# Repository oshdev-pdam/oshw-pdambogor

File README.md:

# oshw-pdambogor

Repositori rintisan untuk OSH Development sensor tekanan air untuk PDAM Kota Bogor

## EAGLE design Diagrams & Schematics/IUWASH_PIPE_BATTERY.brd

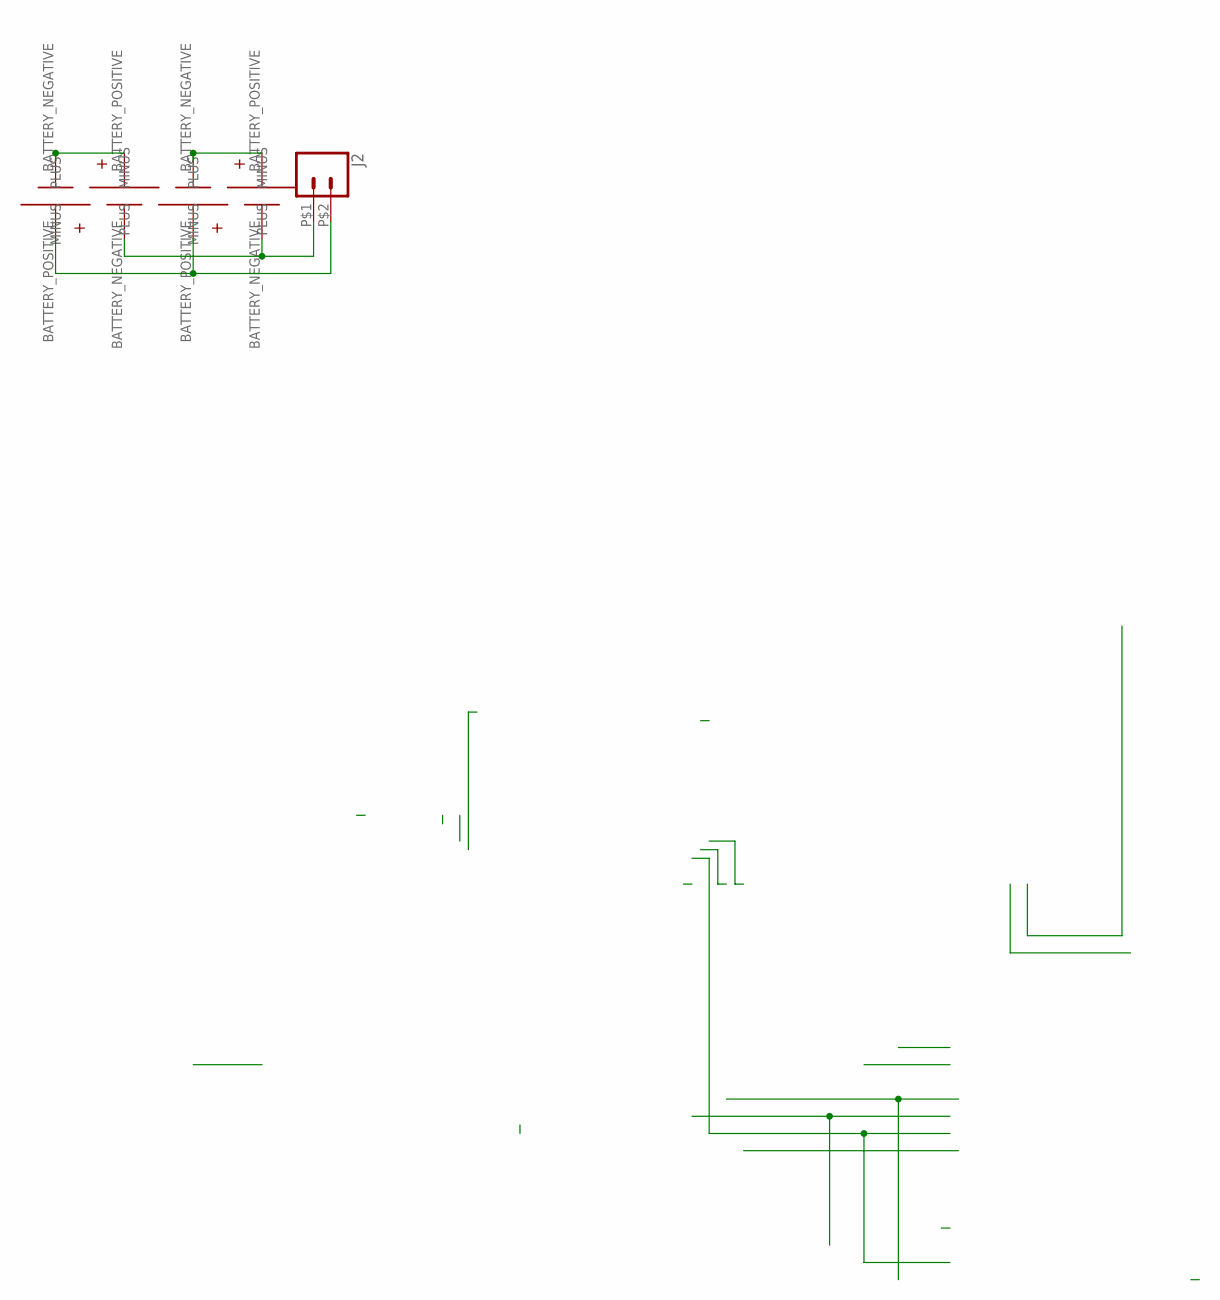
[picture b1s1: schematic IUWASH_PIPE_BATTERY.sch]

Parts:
J2: CONN_02PTH2; 1X02_BIG
U$4, U$5, U$6, U$7: SMT18650; 18650SMT

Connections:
unnamed: J2.P$1 (1), U$5.BATTERY_NEGATIVE (MINUS), U$7.BATTERY_NEGATIVE (MINUS)
unnamed: J2.P$2 (2), U$4.BATTERY_POSITIVE (PLUS), U$6.BATTERY_POSITIVE (PLUS)
unnamed: U$4.BATTERY_NEGATIVE (MINUS), U$5.BATTERY_POSITIVE (PLUS)
unnamed: U$6.BATTERY_NEGATIVE (MINUS), U$7.BATTERY_POSITIVE (PLUS)

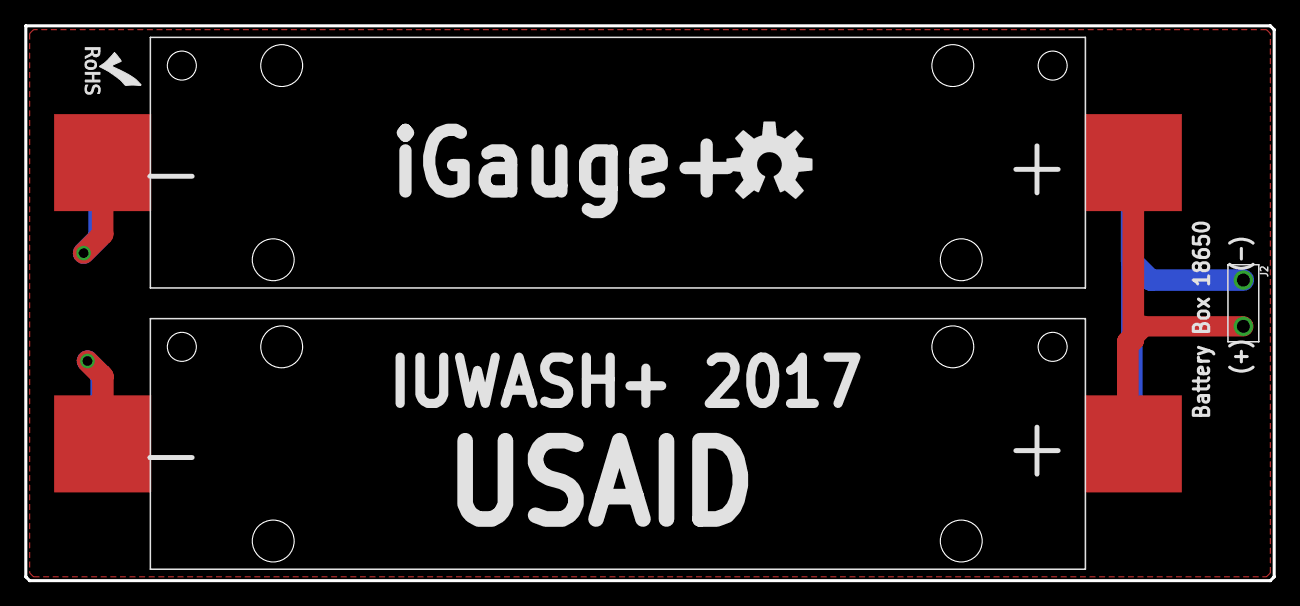
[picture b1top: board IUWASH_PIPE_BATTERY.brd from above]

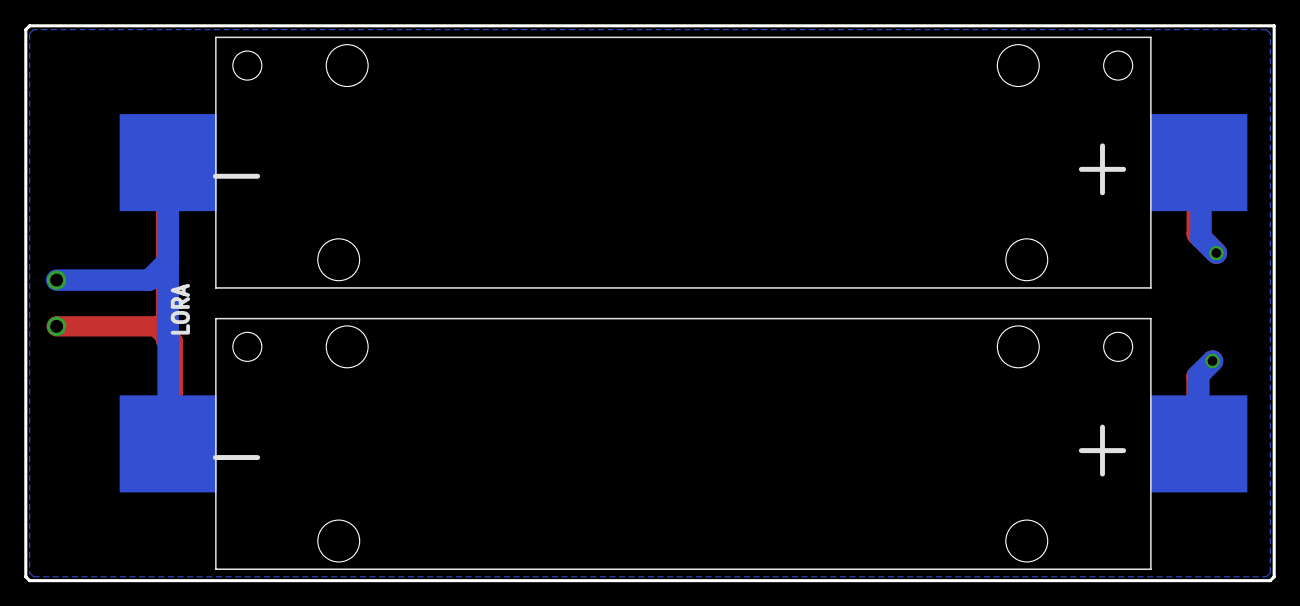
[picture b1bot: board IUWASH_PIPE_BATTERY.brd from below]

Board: 2 copper layers, 102.9 x 45.7 mm, 7 parts (2 on the bottom side), 4 nets.

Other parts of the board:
U$1: OSHW-LOGO-L
U$12: ROHS_LOGO_0.18_IN

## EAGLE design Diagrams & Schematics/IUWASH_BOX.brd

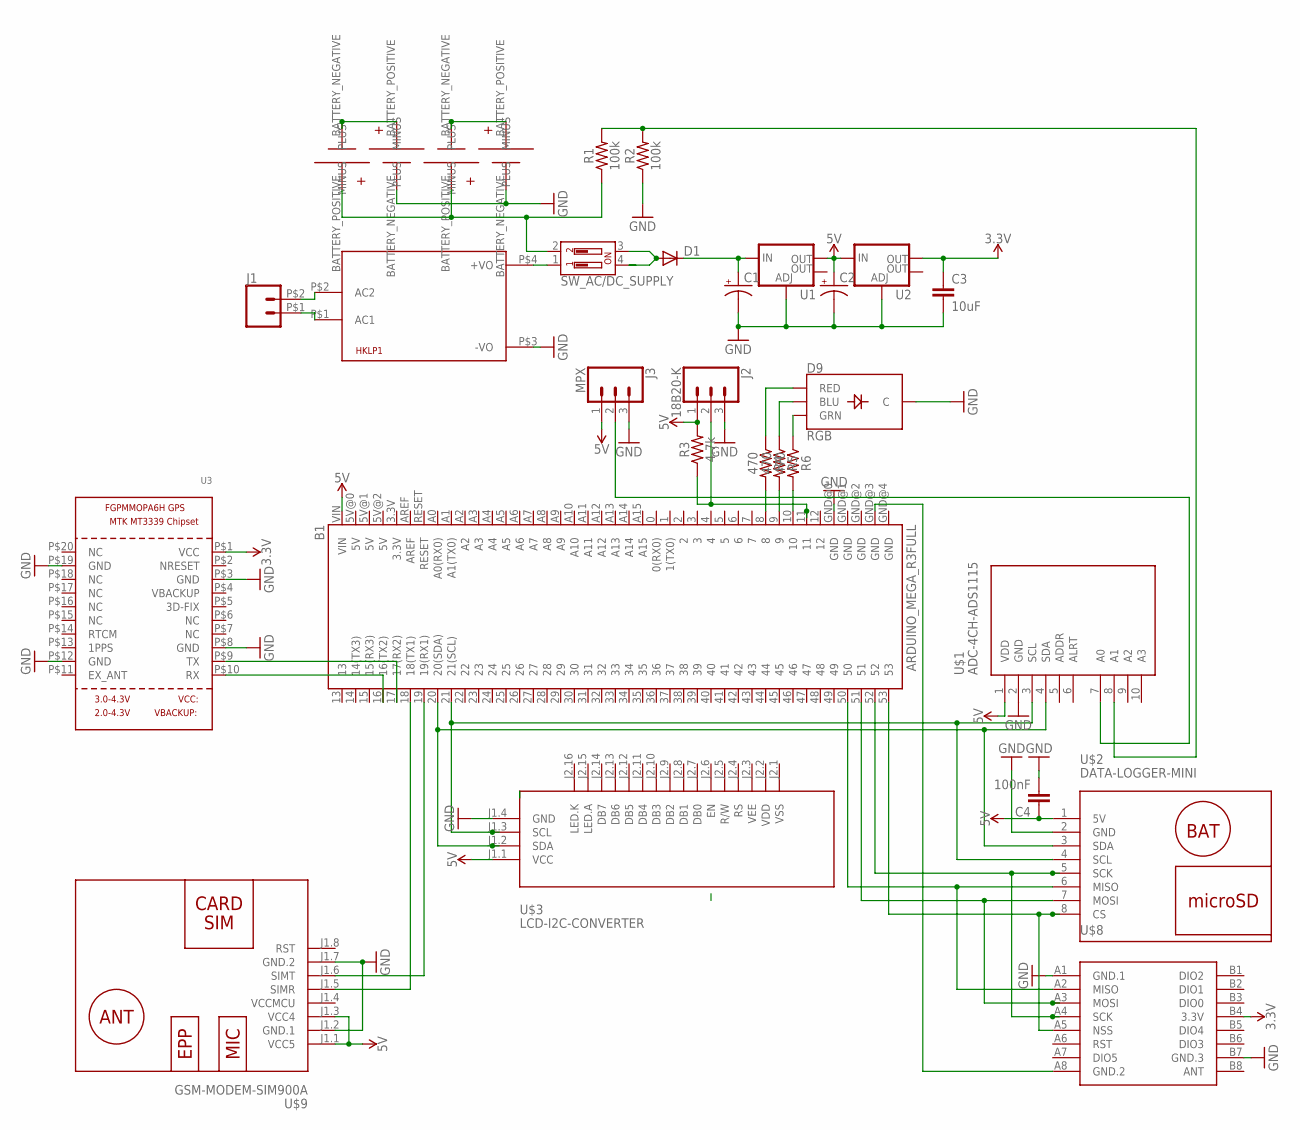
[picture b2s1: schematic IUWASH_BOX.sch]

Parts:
B1: ARDUINO_MEGA_R3FULL; ARDUINO_MEGA
C1, C2: CPOL-USE; PANASONIC_E
C3: 10uF; 0603
C4: 100nF; 0603
D1: DIODE-SOD106-W; SOD106-W
D9: RGB; LED-RGB-THRU
HKLP1: HKLPM01
J1: CONN_02PTH2; 1X02_BIG
J2: 18B20-K; SCREWTERMINAL-3.5MM-3
J3: MPX; SCREWTERMINAL-3.5MM-3
R1, R2: 100k; 0603
R3: 4.7k; 0603
R4, R5, R6: 470; 0603
SW_AC/DC_SUPPLY: DIP-02-PTH-100MIL; DIPSWITCH-02-209-2LPST
U1, U2: V_REG_LM1117SOT223; SOT223
U3: GPS_FGPMMOPA6H; FGPMMOPA6H
U$1: ADC-4CH-ADS1115
U$2: DATA-LOGGER-MINI
U$3: LCD-I2C-CONVERTER
U$4, U$5, U$6, U$7: SMT18650; 18650SMT
U$8: WIRELESS-LORA-RFM95W#SMD
U$9: GSM-MODEM-SIM900A

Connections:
3.3V: C3.1, U2.2 (OUT), U3.P$1 (VCC), U$8.B4 (3.3V)
5V: B1.VIN, C2.+, C4.1, J2.1, J3.1, R3.2, U1.2 (OUT), U2.3 (IN), U$1.1 (VDD), U$2.1 (5V), U$3.J1.1 (VCC), U$9.J1.1 (VCC5), U$9.J1.3 (VCC4)
GND: C4.2, HKLP1.P$3 (-VO), J3.3, R2.1, U3.P$3 (GND), U3.P$8 (GND), U3.P$12 (GND), U3.P$19 (GND), U$2.2 (GND), U$3.J1.4 (GND), U$5.BATTERY_NEGATIVE (MINUS), U$7.BATTERY_NEGATIVE (MINUS), U$8.A1 (GND.1), U$8.B7 (GND.3), U$9.J1.2 (GND.1), U$9.J1.7 (GND.2)
unnamed: C1.+, D1.C, U1.3 (IN)
unnamed: B1.50, U$2.6 (MISO), U$8.A2 (MISO)
unnamed: D1.A, SW_AC/DC_SUPPLY.3, SW_AC/DC_SUPPLY.4
unnamed: HKLP1.P$4 (+VO), SW_AC/DC_SUPPLY.1
unnamed: HKLP1.P$1 (AC1), J1.P$1 (1)
unnamed: HKLP1.P$2 (AC2), J1.P$2 (2)
unnamed: D9.3 (GRN), R6.1
unnamed: J3.2, U$1.7 (A0)
unnamed: R1.1, SW_AC/DC_SUPPLY.2, U$4.BATTERY_POSITIVE (PLUS), U$6.BATTERY_POSITIVE (PLUS)
unnamed: U$4.BATTERY_NEGATIVE (MINUS), U$5.BATTERY_POSITIVE (PLUS)
unnamed: U$6.BATTERY_NEGATIVE (MINUS), U$7.BATTERY_POSITIVE (PLUS)
unnamed: R1.2, R2.2, U$1.8 (A1)
unnamed: B1.17 (17(RX2)), U3.P$9 (TX)
unnamed: B1.52, U$2.5 (SCK), U$8.A4 (SCK)
unnamed: B1.51, U$2.7 (MOSI), U$8.A3 (MOSI)
unnamed: B1.16 (16(TX2)), U3.P$10 (RX)
unnamed: B1.GND@3 (GND), U$8.A8 (GND.2)
unnamed: B1.19 (19(RX1)), U$9.J1.6 (SIMT)
unnamed: B1.20 (20(SDA)), U$1.4 (SDA), U$2.3 (SDA), U$3.J1.2 (SDA)
unnamed: B1.21 (21(SCL)), U$1.3 (SCL), U$2.4 (SCL), U$3.J1.3 (SCL)
unnamed: B1.53, U$2.8 (CS), U$8.A5 (NSS)
unnamed: B1.18 (18(TX1)), U$9.J1.5 (SIMR)
unnamed: B1.8, R4.2
unnamed: B1.11, J2.2, R3.1
unnamed: B1.9, R5.2
unnamed: D9.4 (BLU), R5.1
unnamed: D9.1 (RED), R4.1
unnamed: B1.10, R6.2
unnamed: B1.GND@0 (GND), C1.-, C2.-, C3.2, D9.2 (C), J2.3, U1.1 (ADJ), U2.1 (ADJ), U$1.2 (GND)
VCCMCU: U$9.J1.4 (VCCMCU)

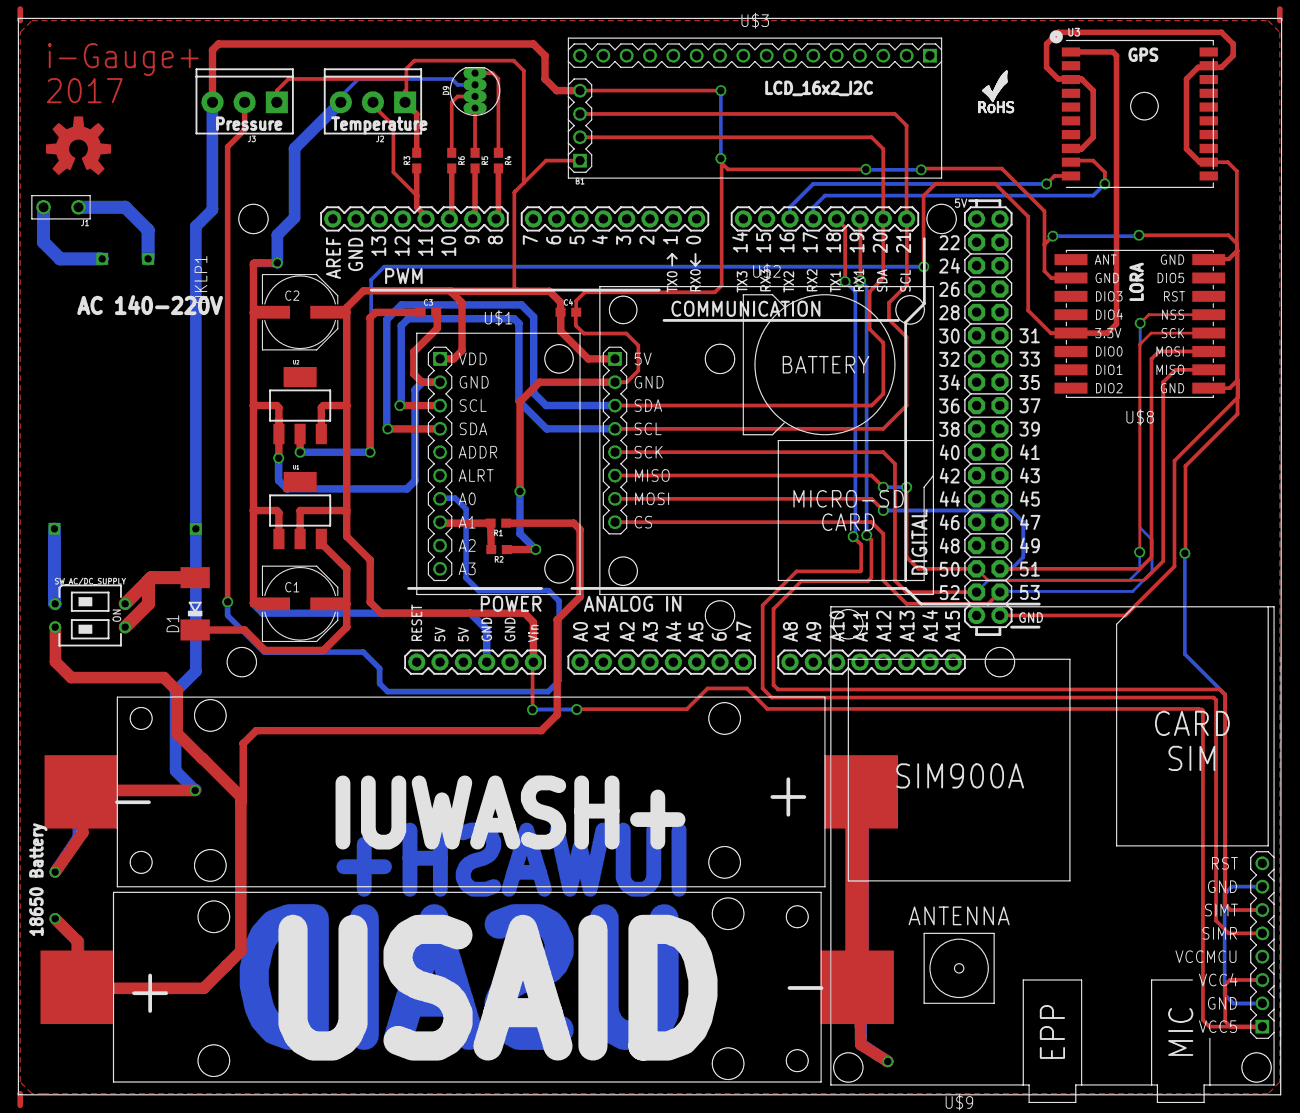
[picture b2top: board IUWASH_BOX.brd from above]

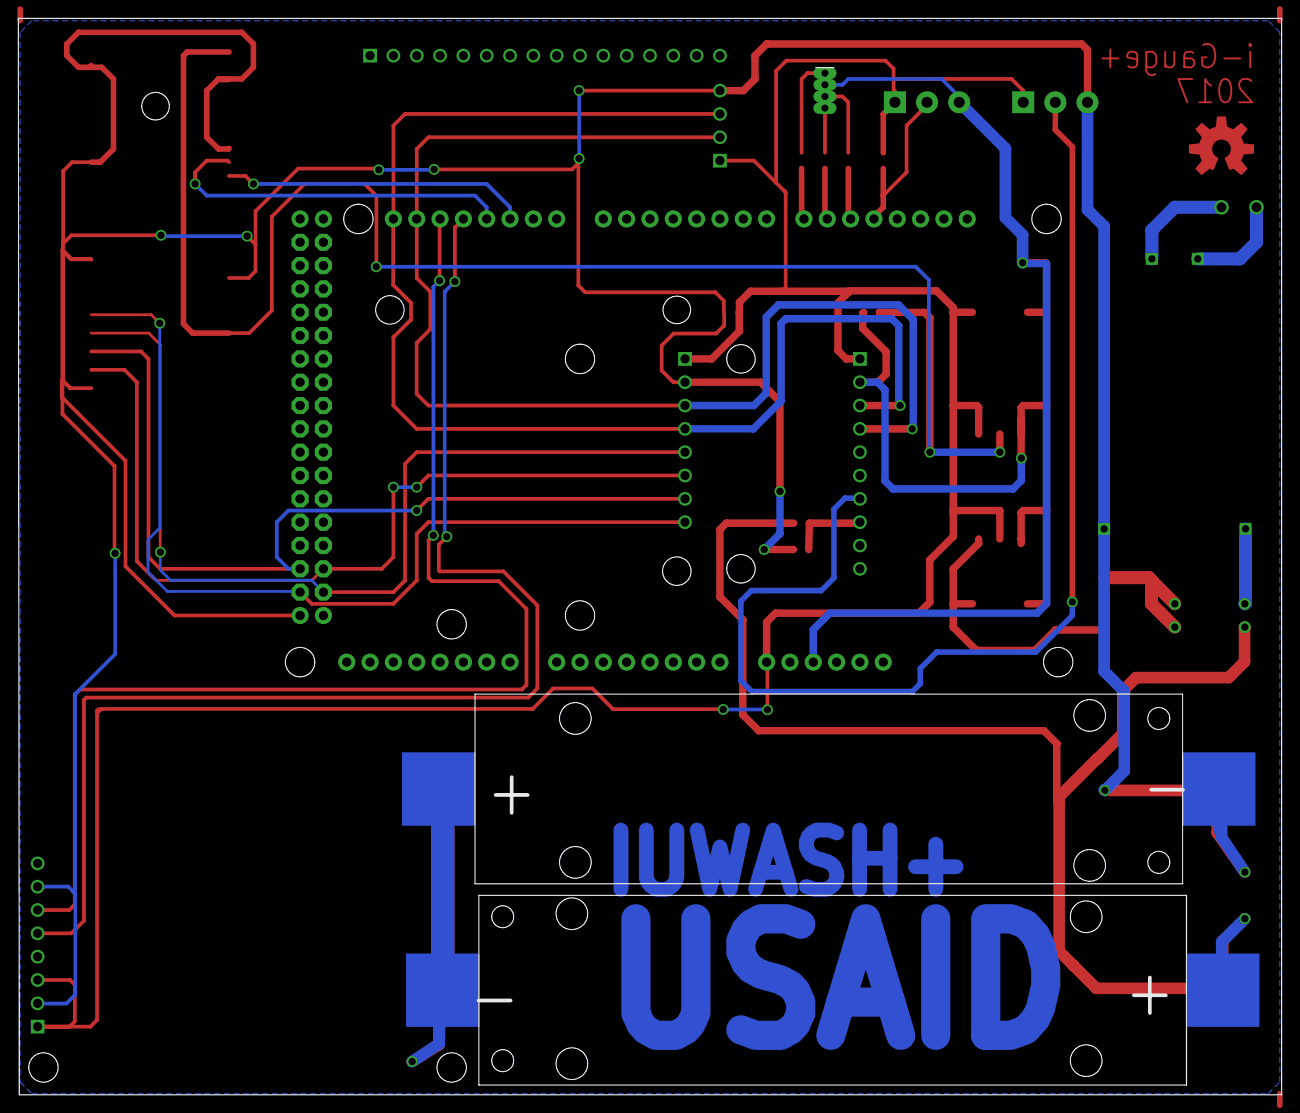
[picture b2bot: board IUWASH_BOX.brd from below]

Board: 2 copper layers, 137.6 x 117.2 mm, 33 parts (2 on the bottom side), 32 nets.

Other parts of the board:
U$10: OSHW-LOGO-L_COPPER
U$11, U$12: ROHS_LOGO_0.18_IN

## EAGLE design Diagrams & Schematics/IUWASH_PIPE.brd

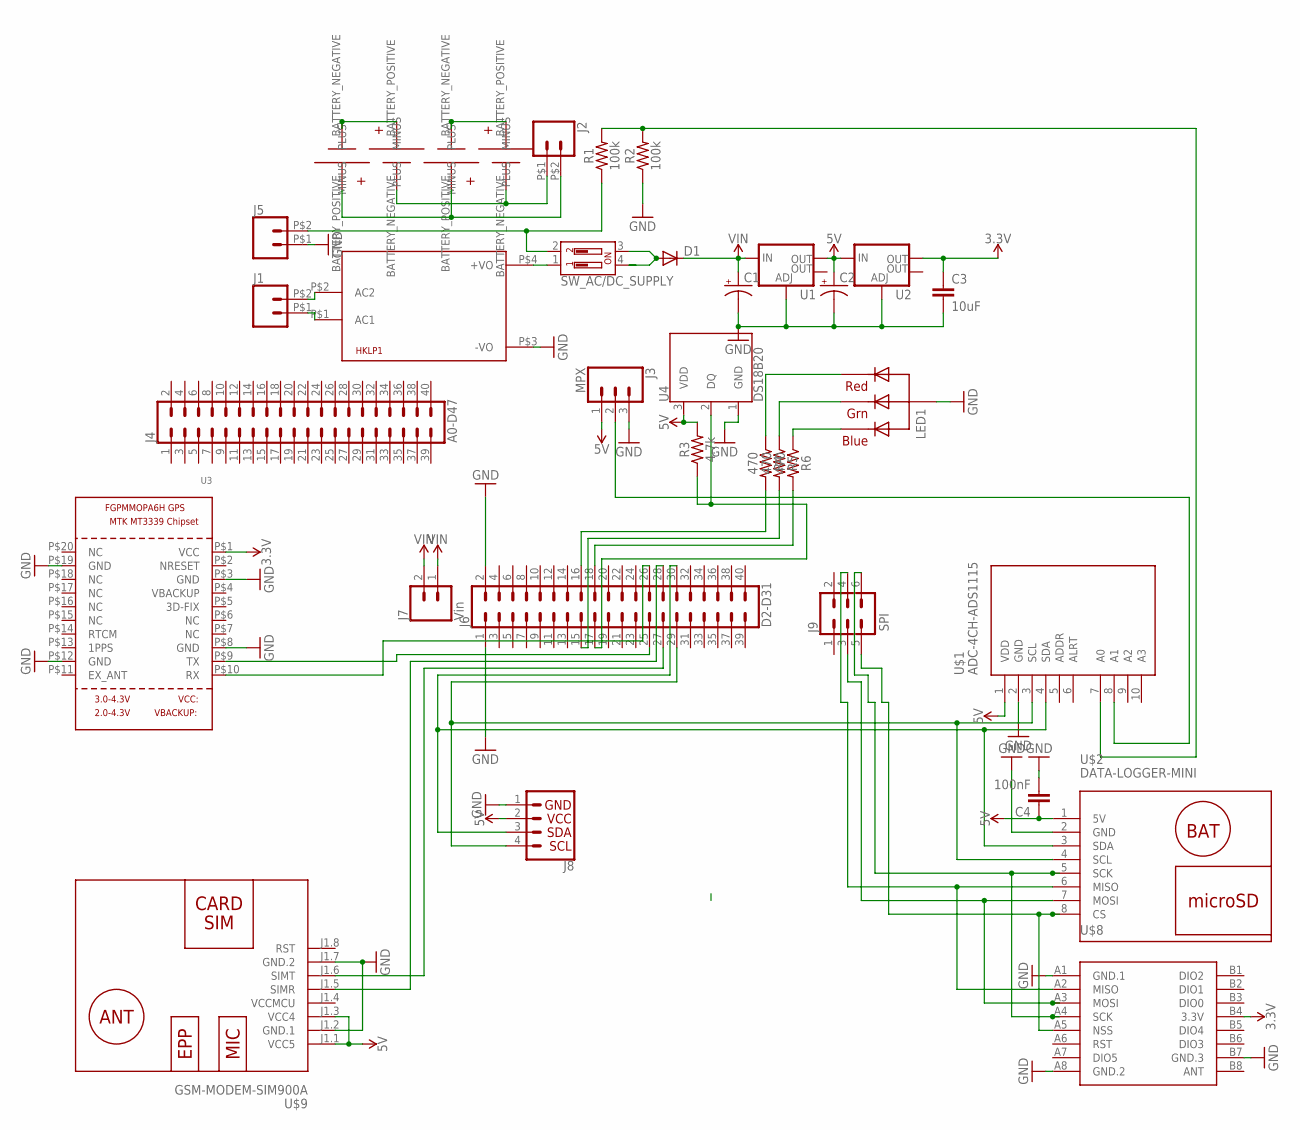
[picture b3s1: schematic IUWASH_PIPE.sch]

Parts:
C1, C2: CPOL-USE; PANASONIC_E
C3: 10uF; 0603
C4: 100nF; 0603
D1: DIODE-SOD106-W; SOD106-W
HKLP1: HKLPM01
J1, J2, J5: CONN_02PTH2; 1X02_BIG
J3: MPX; SCREWTERMINAL-3.5MM-3
J4: A0-D47; 2X20
J6: D2-D31; 2X20
J7: Vin; 1X02
J8: I2C_STANDARD; 1X04
J9: SPI; 2X3
LED1: RGBLED_CA-5MM; LED5MMRGB
R1, R2: 100k; 0603
R3: 4.7k; 0603
R4, R5, R6: 470; 0603
SW_AC/DC_SUPPLY: DIP-02-PTH-100MIL; DIPSWITCH-02-209-2LPST
U1, U2: V_REG_LM1117SOT223; SOT223
U3: GPS_FGPMMOPA6H; FGPMMOPA6H
U4: DS18B20; TO-92-AMMO
U$1: ADC-4CH-ADS1115
U$2: DATA-LOGGER-MINI
U$4, U$5, U$6, U$7: SMT18650; 18650SMT
U$8: WIRELESS-LORA-RFM95W#SMD
U$9: GSM-MODEM-SIM900A

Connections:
1: J8.1
2: J8.2
3.3V: C3.1, U2.2 (OUT), U3.P$1 (VCC), U$8.B4 (3.3V)
5V: C1.+, C2.+, C4.1, D1.C, J3.1, J7.1, J7.2, R3.2, U1.2 (OUT), U1.3 (IN), U2.3 (IN), U4.3 (VDD), U$1.1 (VDD), U$2.1 (5V), U$9.J1.1 (VCC5), U$9.J1.3 (VCC4)
GND: C4.2, HKLP1.P$3 (-VO), J3.3, J5.P$1 (1), J6.1, J6.2, LED1.2 (VCC), R2.1, U3.P$3 (GND), U3.P$8 (GND), U3.P$12 (GND), U3.P$19 (GND), U$1.2 (GND), U$2.2 (GND), U$8.A1 (GND.1), U$8.A8 (GND.2), U$8.B7 (GND.3), U$9.J1.2 (GND.1), U$9.J1.7 (GND.2)
unnamed: J2.P$1 (1), U$5.BATTERY_NEGATIVE (MINUS), U$7.BATTERY_NEGATIVE (MINUS)
unnamed: J9.4, U$2.6 (MISO), U$8.A2 (MISO)
unnamed: D1.A, SW_AC/DC_SUPPLY.3, SW_AC/DC_SUPPLY.4
unnamed: HKLP1.P$4 (+VO), SW_AC/DC_SUPPLY.1
unnamed: HKLP1.P$1 (AC1), J1.P$1 (1)
unnamed: HKLP1.P$2 (AC2), J1.P$2 (2)
unnamed: LED1.4 (BLUE), R6.1
unnamed: J3.2, U$1.8 (A1)
unnamed: J2.P$2 (2), U$4.BATTERY_POSITIVE (PLUS), U$6.BATTERY_POSITIVE (PLUS)
unnamed: U$4.BATTERY_NEGATIVE (MINUS), U$5.BATTERY_POSITIVE (PLUS)
unnamed: U$6.BATTERY_NEGATIVE (MINUS), U$7.BATTERY_POSITIVE (PLUS)
unnamed: R1.2, R2.2, U$1.7 (A0)
unnamed: J6.25, U3.P$9 (TX)
unnamed: J5.P$2 (2), R1.1, SW_AC/DC_SUPPLY.2
unnamed: J9.6, U$2.5 (SCK), U$8.A4 (SCK)
unnamed: J9.3, U$2.7 (MOSI), U$8.A3 (MOSI)
unnamed: J6.26, U3.P$10 (RX)
unnamed: J6.27, U$9.J1.6 (SIMT)
unnamed: J6.30, J8.3, U$1.4 (SDA), U$2.3 (SDA)
unnamed: J6.29, J8.4, U$1.3 (SCL), U$2.4 (SCL)
unnamed: J9.5, U$2.8 (CS), U$8.A5 (NSS)
unnamed: J6.28, U$9.J1.5 (SIMR)
unnamed: J6.16, R4.2
unnamed: J6.17, R3.1, U4.2 (DQ)
unnamed: J6.15, R5.2
unnamed: LED1.3 (GREEN), R5.1
unnamed: LED1.1 (RED), R4.1
unnamed: J6.18, R6.2
unnamed: C1.-, C2.-, C3.2, U1.1 (ADJ), U2.1 (ADJ), U4.1 (GND)
VCCMCU: U$9.J1.4 (VCCMCU)

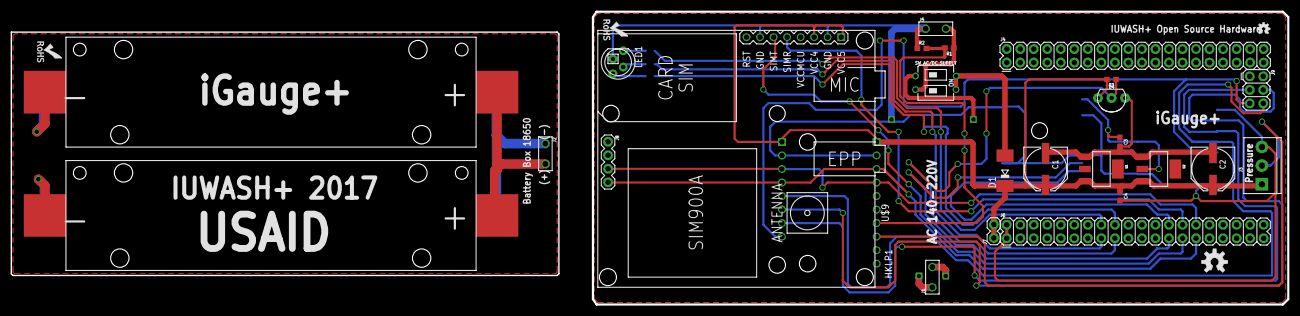
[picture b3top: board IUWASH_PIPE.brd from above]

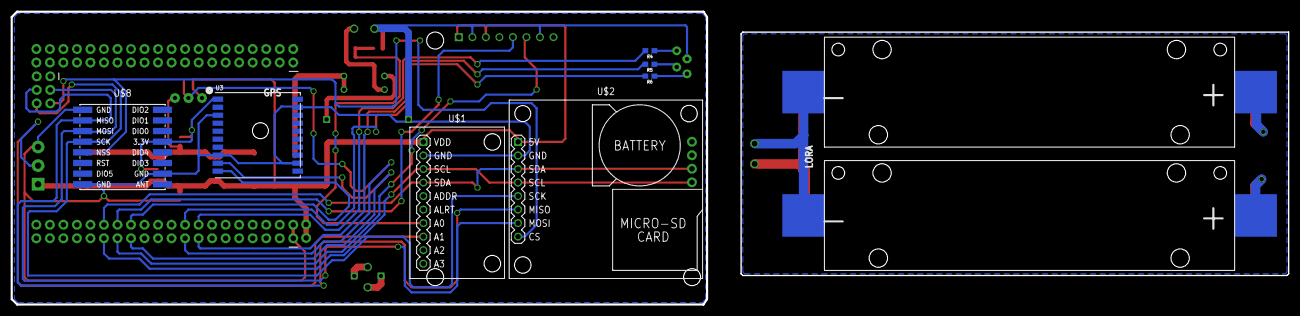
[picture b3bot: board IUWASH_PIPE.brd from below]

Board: 2 copper layers, 239.8 x 55.0 mm, 39 parts (9 on the bottom side), 32 nets.

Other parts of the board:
U$3: OSHW-LOGO-M
U$10: OSHW-LOGO-MINI
U$11, U$12: ROHS_LOGO_0.18_IN

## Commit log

2017-10-16 Reorganize Repository into neat folders
2017-10-16 Lupa add
2017-10-18 Create box type
2017-10-18 rollback
2017-10-18 re-push: add .brd and .sch files
2017-10-23 USER'S JOURNEY
2017-10-27 Arduino_Mega
2017-10-27 Proteus
2017-10-27 Proteus_2
2017-12-05 Create src
2017-12-05 arduino
2018-02-24 Arduino script
2018-03-07 Sleep mode

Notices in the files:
parts and their libraries:
SparkFun-Boards: Licensing: Creative Commons ShareAlike 4.0 International - https://creativecommons.org/licenses/by-sa/4.0
diy-modules: Released under the Creative Commons Attribution 4.0 International License: http://creativecommons.org/licenses/by/4.0
